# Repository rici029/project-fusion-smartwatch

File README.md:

# InkTime - Smartwatch Open Source

InkTime este un smartwatch ieftin, open-source, construit in jurul microcontroller-ului **Nordic nRF52840** (BLE 5 + ARM Cortex-M4) si a unui display **e-paper de 1.54"**. Consumul redus al e-paper-ului combinat cu eficienta nRF-ului permite o autonomie de cateva zile pe o baterie LiPo mica.

---

## Cuprins

- [Diagrama bloc](#diagrama-bloc)
- [Descriere hardware](#descriere-hardware)
- [Bill of Materials (BOM)](#bill-of-materials-bom)
- [Pin mapping nRF52840](#pin-mapping-nrf52840)
- [Estimare consum energie](#estimare-consum-energie)
- [Design mecanic](#design-mecanic)
- [Design log](#design-log)
- [Structura repository-ului](#structura-repository-ului)
- [Licenta](#licenta)

---

## Diagrama bloc

Arhitectura dispozitivului se bazeaza pe nRF52840 ca hub central. Acesta comunica cu:

- **Display e-paper** prin SPI + semnale de control (DC/RST/BUSY)
- **Accelerometrul BMA423** prin I2C (pentru detectarea miscarii si step counter)
- **PMIC BQ25180** prin I2C (management incarcare baterie Li-Ion)
- **Driver haptic DRV2605** prin I2C (feedback vibrator)
- **USB-C** pentru incarcare si comunicatie seriala (USB nativ al nRF)
- **3 butoane** pe GPIO-uri dedicate
- **Antena chip 2.4GHz** pentru BLE

Alimentarea este furnizata de un buck-boost **RT6160** care genereaza 3.3V stabil din baterie (domeniu tipic 3.0-4.2V).

---

## Descriere hardware

### Microcontroller - Nordic nRF52840

- **Core:** ARM Cortex-M4F @ 64 MHz
- **Memorie:** 1 MB Flash + 256 KB RAM
- **Radio:** BLE 5.3, 2.4 GHz, puterea TX pana la +8 dBm
- **Interfete:** USB 2.0 Full Speed nativ, SPI, I2C, UART, I2S, PDM, QSPI
- **Justificare alegere:** consum redus (~5 uA in System OFF cu RAM retinuta), suport BLE complet, USB nativ care elimina nevoia de USB-to-Serial

### Power Management

**BQ25180 - Battery Charger (IC1)**
- Incarcator Li-Ion de 1 celula, pana la 550 mA
- Protectii integrate: OVP, SCP, termica
- Control prin I2C - poate raporta starea bateriei si curentul de incarcare
- Pin ALERT (interrupt) catre nRF pentru notificare evenimente

**RT6160 - Buck-Boost DC/DC (IC2)**
- Intrare: 2.5-5.5V (acopera atat VBAT cat si VBUS de la USB)
- Iesire: 3.3V (VREG -> 3V3 rail intern)
- Eficienta >90% la sarcini tipice
- Iesirea VSEL configurabila digital

### Senzori

**BMA423 - Accelerometru 3-axe (IC3)**
- 16-bit, range +/-2/+/-4/+/-8/+/-16 g
- Consum ultra-low: ~3 uA in low-power mode
- Features integrate: step counter, wake-on-tilt, activity recognition
- Comunicatie: I2C
- Doua interrupt-uri (INT1, INT2) pentru wake-up asincron al nRF

### Haptic Feedback

**DRV2605 - Haptic Driver (IC4)**
- Driver pentru motor ERM/LRA (shaker coin motor)
- Librarie integrata de 123 efecte preset
- Control I2C + enable digital (HAPTIC_EN)

### Display

**E-paper 1.54" (model WSH-12561, 200x200 pixel)**
- Conectat prin SPI (MOSI, SCK, EPD_CS) + 3 semnale control (DC, RST, BUSY)
- Circuit de boost integrat - foloseste componentele externe EPD_C1..EPD_C12 (condensatoare + inductor L2, L3 + diode D1-D3 pentru generarea PREVGL/PREVGH/GDR)
- Activare alimentare 3.3V prin MOSFET Q2 controlat de EPD_CS

### USB si protectie

**Conector USB-C (J3)** cu 16 pini (reversibil)
**USBLC6-2SC6Y (D4)** - ESD protection pe liniile D+/D-
Conectare directa la nRF52840 (USB nativ integrat)

### Circuit RF

Antena **2450AT18B100E** (Johanson) cu pi-network de matching:
- **C13, C15, C16** - condensatoare de acord
- **L4 (3.9 nH)** - inductor de matching
- **X1 (32 MHz)** - cristal pentru PLL radio, cu condensatoare de sarcina (12pF)
- **X2 (32.768 kHz)** - cristal pentru RTC (wake-up periodic low-power)

---

## Bill of Materials (BOM)

| Ref | Componenta | Valoare / Model | Capsula | Link JLC Parts | Datasheet |
|-----|------------|-----------------|---------|----------------|-----------|
| IC - nRF | Microcontroller | nRF52840-QIAA | aQFN73 | [JLC](https://jlcpcb.com/parts) | [PDF](https://infocenter.nordicsemi.com/pdf/nRF52840_PS_v1.7.pdf) |
| IC1 | Battery Charger PMIC | BQ25180 | WCSP-8 | [JLC](https://jlcpcb.com/parts) | [PDF](https://www.ti.com/lit/ds/symlink/bq25180.pdf) |
| IC2 | Buck-Boost DC/DC | RT6160A | WQFN-15 | [JLC](https://jlcpcb.com/parts) | [PDF](https://www.richtek.com/assets/product_file/RT6160A/DS6160A-00.pdf) |
| IC3 | Accelerometer | BMA423 | LGA-12 | [JLC](https://jlcpcb.com/parts) | [PDF](https://www.bosch-sensortec.com/media/boschsensortec/downloads/datasheets/bst-bma423-ds000.pdf) |
| IC4 | Haptic Driver | DRV2605 | WCSP-9 | [JLC](https://jlcpcb.com/parts) | [PDF](https://www.ti.com/lit/ds/symlink/drv2605.pdf) |
| U1 | Fuel Gauge | (MAX17048 / LC709203) | WCSP-8 | [JLC](https://jlcpcb.com/parts) | [PDF](https://www.analog.com/media/en/technical-documentation/data-sheets/MAX17048-MAX17049.pdf) |
| ANT1 | Chip Antenna 2.4GHz | 2450AT18B100E | SMD | [JLC](https://jlcpcb.com/parts) | [PDF](https://www.johansontechnology.com/datasheets/2450AT18B100/2450AT18B100.pdf) |
| X1 | Cristal | 32 MHz | 3.2x2.5 mm | [JLC](https://jlcpcb.com/parts) | - |
| X2 | Cristal | 32.768 kHz | 3.2x1.5 mm | [JLC](https://jlcpcb.com/parts) | - |
| L1 | Inductor DC/DC | MLP2016 470nH | 2016 | [JLC](https://jlcpcb.com/parts) | - |
| L2 | Inductor E-paper | 10 uH | 0603 | [JLC](https://jlcpcb.com/parts) | - |
| L3 | Inductor E-paper | 15 uH | 0603 | [JLC](https://jlcpcb.com/parts) | - |
| L4 | Inductor RF matching | 3.9 nH | 0201 | [JLC](https://jlcpcb.com/parts) | - |
| Q2 | MOSFET P-channel | (EPD power switch) | SOT-23 | [JLC](https://jlcpcb.com/parts) | - |
| D1-D3 | Dioda Schottky | (boost converter) | SOD-323 | [JLC](https://jlcpcb.com/parts) | - |
| D4 | ESD USB Protection | USBLC6-2SC6Y | SOT-23-6 | [JLC](https://jlcpcb.com/parts) | [PDF](https://www.st.com/resource/en/datasheet/usblc6-2.pdf) |
| J1 | SWD Programming | TC2030-IDC | THT | [JLC](https://jlcpcb.com/parts) | [PDF](https://www.tag-connect.com/wp-content/uploads/bsk-pdf-manager/TC2030-IDC_Datasheet_14.pdf) |
| J2 | FPC Connector | 503480-2400 (24p) | SMD | [JLC](https://jlcpcb.com/parts) | [PDF](https://www.molex.com/pdm_docs/sd/5034802400_sd.pdf) |
| J3 | USB-C | KH-TYPE-C-16P | SMD | [JLC](https://jlcpcb.com/parts) | - |
| SW1-3 | Buton tactil | SMD side-push | SMD | [JLC](https://jlcpcb.com/parts) | - |
| Baterie | LiPo 3.7V | AKY0106 | - | - | [PDF](https://www.tme.eu/Document/b9e12bf26ad0ba929a22ab5d58f022cd/AKY0106.pdf) |
| Display | E-paper 1.54" | WSH-12561 | FPC | - | [PDF](https://www.tme.eu/Document/0ca57a8ffbcd57b5bca53252eb9d6ec3/WSH-12561.pdf) |
| Shaker | Motor vibrator | DFRobot FIT0774 | coin | - | [link](https://www.tme.eu/ro/details/df-fit0774/motoare-dc/dfrobot/fit0774/) |

**Condensatoare si rezistente:** toate in capsule 0201 (pentru valori <= 100 nF) sau 0402 (pentru valori > 100 nF), conform cerintei proiectului. Vezi fisierul `Manufacturing/bom.txt` pentru lista completa cu referinte si valori.

---

## Pin mapping nRF52840

| Pin nRF52840 | Net / Semnal | Functie | Motivatie alegere |
|--------------|--------------|---------|-------------------|
| P0.26 | SCL | I2C Clock | Pin GPIO standard, aproape de IC-urile I2C (BMA423, BQ25180, DRV2605) pentru trase scurte |
| P0.27 | SDA | I2C Data | Pereche cu P0.26 pentru TWI0 |
| P0.04 | IMU_INT1 | Interrupt BMA423 | Pin cu capabilitate AIN (ADC) dar folosit ca GPIO - pozitie convenabila pe PCB |
| P0.13 | SCK | SPI Clock (E-paper) | High-speed GPIO, suport SPIM |
| P0.14 | MOSI | SPI Data (E-paper) | Pereche cu SCK pe aceeasi periferica SPIM |
| P0.19 | EPD_CS | Chip Select e-paper | GPIO simplu, control SPI CS |
| P0.20 | EPD_DC | Data/Command | Control semnal pentru display |
| P0.21 | EPD_RST | Reset e-paper | GPIO cu output drive standard |
| P0.22 | EPD_BUSY | Busy signal | Input de la display, pentru polling |
| P0.23 | HAPTIC_EN | Enable DRV2605 | GPIO simplu, activeaza driver-ul haptic |
| P0.24 | PMIC_INT | Interrupt BQ25180 | Interrupt la evenimente de charging |
| P0.25 | ALERT | Alert fuel gauge | Notificare low-battery |
| P0.09, P0.10 | SW1, SW2 (Buttons) | Butoane utilizator | Pini dedicati cu suport NFC dezactivat (configurabili GPIO) |
| P1.09 | SW3 | Al treilea buton | GPIO free pe portul P1 |
| P1.01 | IMU_INT2 | Interrupt secundar BMA423 | GPIO free |
| SWDIO, SWDCLK | TP + J1 | Programming / Debug | Pini dedicati SWD, accesibili prin TC2030 si test pad-uri |
| XL1, XL2 | X2 (32.768 kHz) | LFCLK pentru RTC | Pini dedicati oscilatorului low-frequency |
| XC1, XC2 | X1 (32 MHz) | HFCLK pentru radio | Pini dedicati oscilatorului high-frequency |
| D+/D- | USB | USB native | Pini dedicati, conectati direct la USB-C prin USBLC6 |
| ANT | ANT1 | Antena BLE | Pin RF dedicat, conectat prin reteaua de matching |

**Nota:** Pinii ADC (P0.02-P0.05, P0.28-P0.31) care nu sunt folositi ca AIN sunt disponibili pentru extensii viitoare (ex: senzori analogici aditionali).

---

## Estimare consum energie

| Mod de operare | Componente active | Consum estimat |
|----------------|-------------------|----------------|
| Sleep (System OFF + RAM) | nRF RAM retained + RTC + BMA423 low-power | **~10 uA** |
| Idle (display static, BLE advertising) | nRF BLE adv + RTC + IMU | **~50 uA** |
| Active (refresh display) | nRF MCU on + SPI + EPD boost | ~8 mA (~500 ms per refresh) |
| BLE connected (data transfer) | nRF radio TX/RX @ 0 dBm | ~5-8 mA |
| Charging | BQ25180 la 500 mA | de la USB, nu de la baterie |

**Autonomie estimata:**  
Baterie tipica: ~110 mAh (AKY0106).  
Cu consum mediu ~50 uA (majoritatea timpului in idle + cateva refresh-uri de display pe ora):

T_autonomie = 110 mAh / 0.05 mA = 2200 ore ~ 90 zile

In practica, cu uzura normala (notificari, interactiuni cu butoanele, sync BLE), **durata de viata realista pe baterie este de ~2-4 saptamani**.

---

## Design mecanic

Dispozitivul este construit din:
- **PCB 1 mm grosime**, 4 layere (Top + 2 Inner GND + Bottom)
- **Carcasa** cu TopCase (rama + fereastra display) + BottomCase (compartiment baterie)
- **Baterie LiPo** plasata sub PCB in compartimentul BottomCase
- **Display e-paper** montat deasupra PCB, aliniat cu fereastra TopCase
- **Shaker motor** plasat lateral, conectat la PCB prin pad-uri TP_OUT+/OUT-
- **3 butoane fizice** aliniate cu SW1-SW3 pe PCB

Bateria se conecteaza direct la 2 test pad-uri (TP_BAT / TP_GND) in loc sa foloseasca conectorul JST original, pentru a economisi spatiu.

---

## Design log

### Decizii importante luate

1. **Alegerea stack-up-ului 4 layere:** desi un design 2-layer ar fi fost posibil, am optat pentru 4 layere cu doua planuri GND interne (Optiunea B). Motivele:
   - Return path continuu pentru semnalele SPI (display) si USB D+/D-
   - Performanta RF mai buna pentru circuitul BLE 2.4 GHz
   - Simplificare rutare - nu mai trebuie evitate via-urile pe trasee de putere
   - Ecranare EMI imbunatatita intre TOP si BOTTOM

2. **Rutarea 3V3 ca trasee groase (nu plane):** pentru ca 3V3 e consumator redus (< 100 mA) am preferat trasee groase (0.3 mm) pe TOP/BOTTOM in loc de un plane intern. Inner layers raman ambele GND.

3. **Antena la marginea PCB-ului + decupare:** am plasat antena 2450AT18B100E la marginea placii, cu zona de sub ea **decupata mecanic** si fara cupru pe niciun layer (conform datasheet si cerintei). In jurul antenei am adaugat via stitching pentru a lega planurile GND.

4. **Keepout pe toate cele 4 layere sub antena:** am desenat dreptunghiuri pe tRestrict, bRestrict si echivalentele pentru inner layers, plus decupare pe Dimension/Milling.

5. **Via stitching in zona RF:** plasate via-uri GND (0.3 mm drill / 0.6 mm diametru) la ~1.5 mm distanta in jurul nRF52840 si antenei pentru continuitate planuri GND.

6. **Plasarea condensatoarelor de decuplare:** toate cele 100 nF sunt plasate in capsula 0201 direct langa pinii VDD ai nRF, BMA423, DRV2605, BQ25180 si RT6160.

### Probleme intampinate

- **Rutare sub BGA nRF52840:** pinii interni ai BGA-ului au spatiere foarte mica; traseele de intrare/iesire din zona BGA au fost ingustate la 0.127 mm pentru a se incadra intre bile. Au aparut erori DRC "width too small" dar sunt acceptate conform cerintei.
- **Spatiu limitat pentru rutare:** placa de smartwatch fiind compacta (~35x40 mm), am trecut la 4 layere pentru a avea suficient spatiu de rutare.
- **Orientarea FPC-ului display-ului:** conectorul J2 a fost orientat astfel incat cablul flat sa aiba lungime minima pana la display, fara bucle.
- **Net classes aplicate dupa ce am inceput rutarea:** am adaugat clasa "Power" cu width 0.3 mm dupa ce rutasem deja cateva trasee la 0.15 mm. Am folosit comanda CHANGE WIDTH pentru a le ingrosa.

---

## Structura repository-ului

```
InkTime/
├── Hardware/
│   ├── InkTime_Schematic.sch     # Schematicul Fusion
│   ├── InkTime_Schematic.brd     # Board-ul Fusion
│   └── InkTime_Schematic.pdf     # Print-out schematic
├── Manufacturing/
│   ├── gerbers.zip               # Fisiere Gerber + Drill
│   ├── bom.txt                   # Bill of Materials
│   └── cpl.txt                   # Pick and Place
├── Mechanical/
│   ├── complete_device.step      # Model 3D exploded
│   └── complete_device.f3z       # Fisier Fusion Design complet
├── Images/
│   ├── block_diagram.png
│   ├── pcb_top.png
│   ├── pcb_bottom.png
│   ├── pcb_3d_top.png
│   └── device_3d.png
├── LICENSE                       # Apache 2.0
└── README.md
```

---

## Licenta

Acest proiect este licentiat sub **Apache License 2.0**. Vezi fisierul [LICENSE](LICENSE) pentru detalii.

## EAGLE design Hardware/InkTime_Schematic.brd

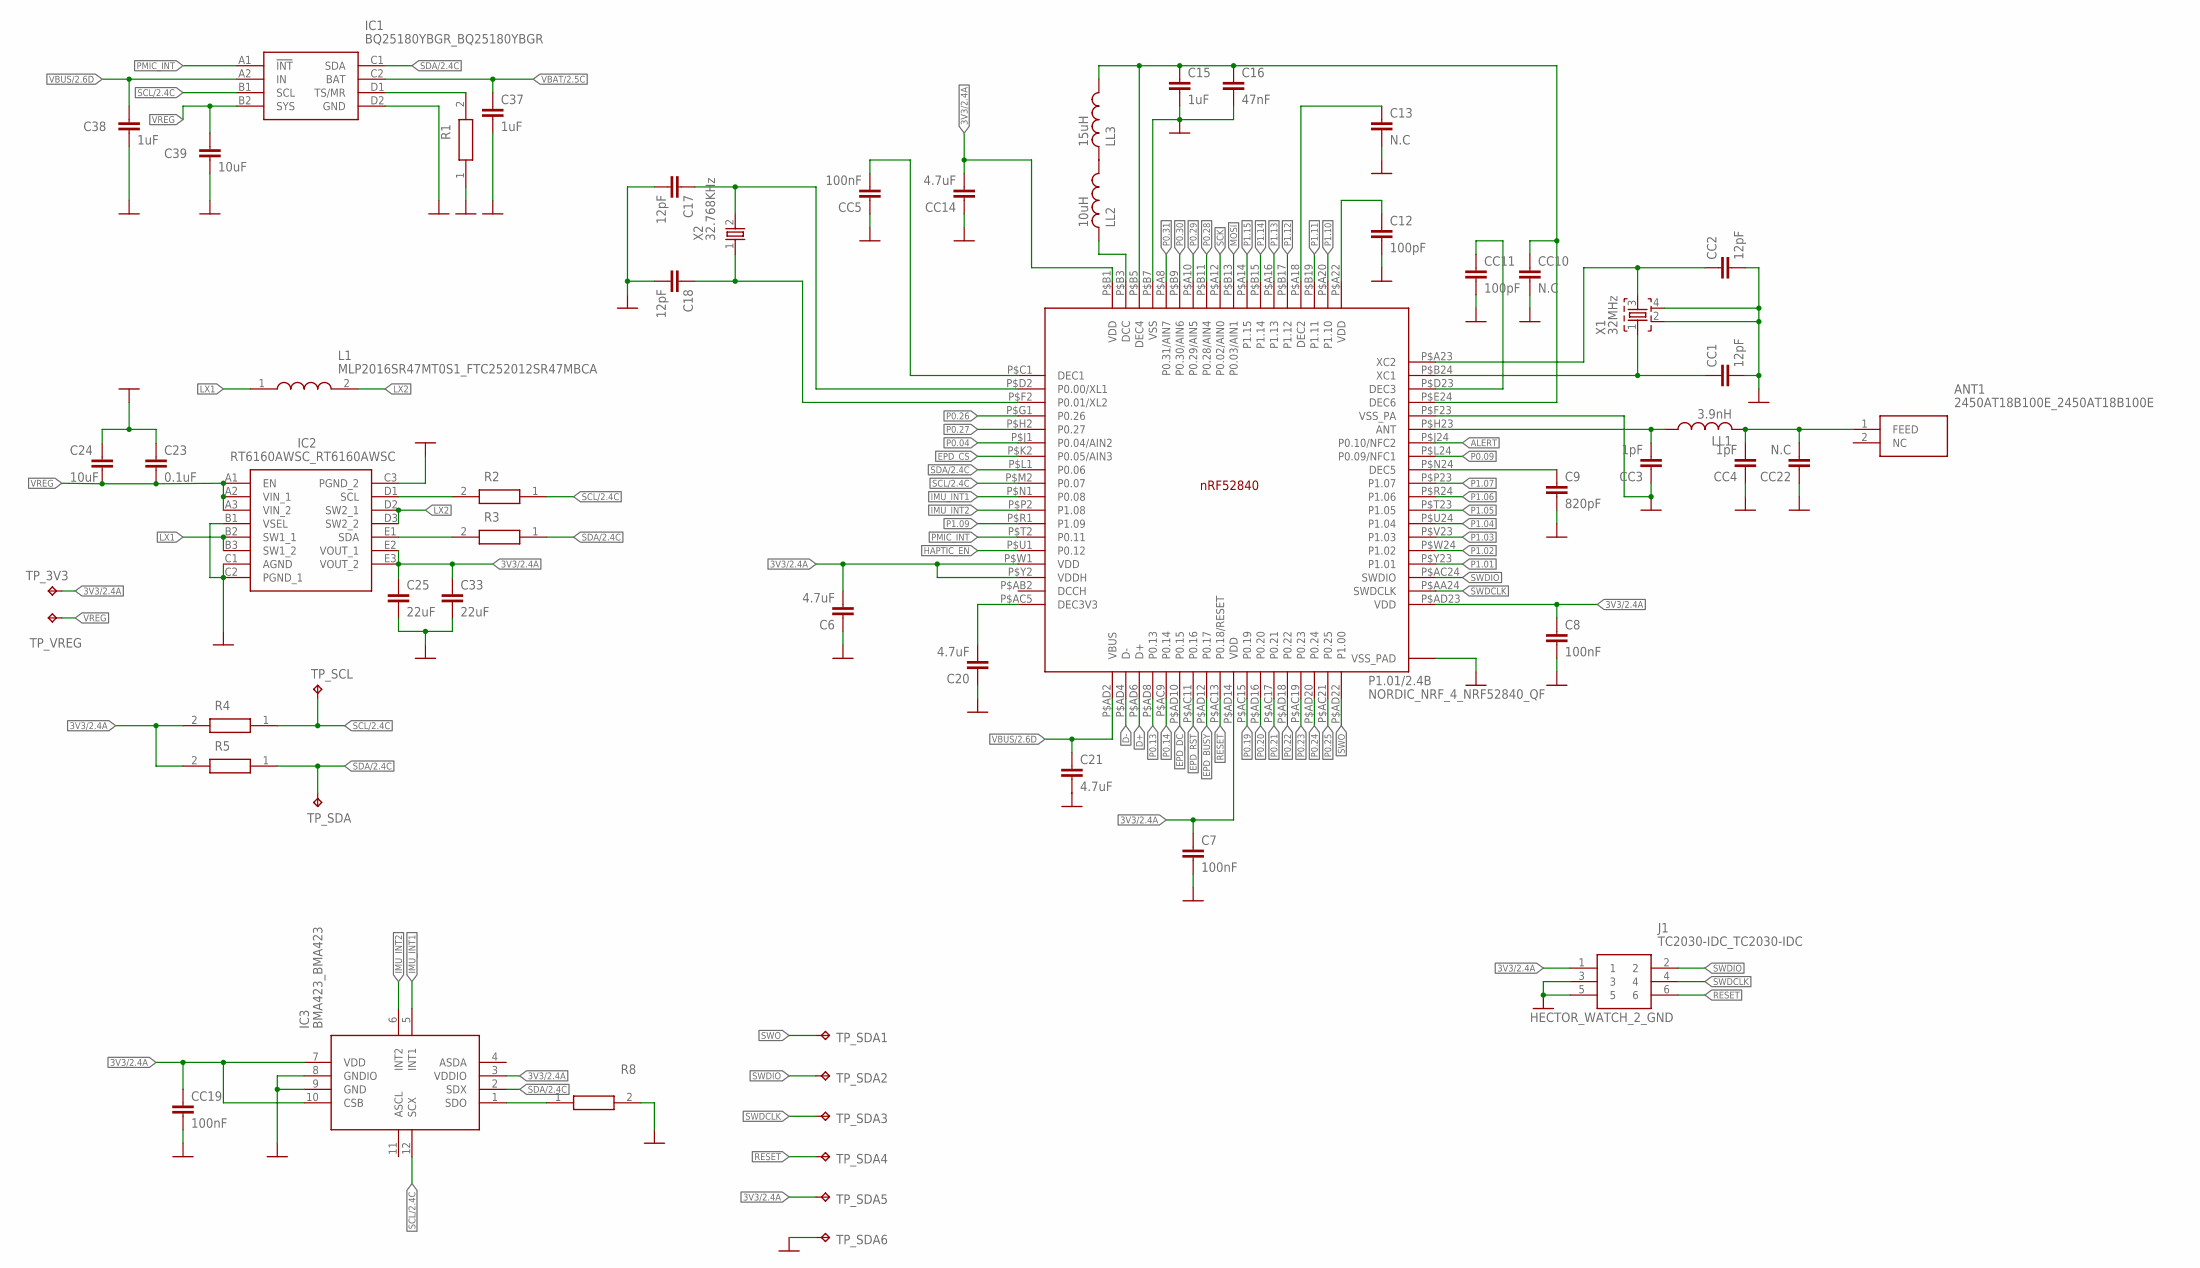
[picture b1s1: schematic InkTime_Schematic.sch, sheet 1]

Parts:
ANT1: 2450AT18B100E_2450AT18B100E; 2450AT18B100E_ANTC3216X140N
C6, C20, C21: 4.7uF; NORDIC_NRF_3_RESC0402_M
C7, C8: 100nF; NORDIC_NRF_3_RESC0402_M
C9: 820pF; NORDIC_NRF_3_RESC0402_M
C12: 100pF; NORDIC_NRF_3_RESC0402_M
C13: N.C; NORDIC_NRF_3_RESC0402_M
C15, C37, C38: 1uF; NORDIC_NRF_3_RESC0402_M
C16: 47nF; NORDIC_NRF_3_RESC0402_M
C17, C18: 12pF; NORDIC_NRF_3_RESC0402_M
C23: 0.1uF; NORDIC_NRF_3_RESC0402_M
C24, C39: 10uF; NORDIC_NRF_3_RESC0402_M
C25, C33: 22uF; NORDIC_NRF_3_RESC0402_M
CC1, CC2: 12pF; NORDIC_NRF_3_RESC0402_M
CC3, CC4: 1pF; NORDIC_NRF_3_RESC0402_M
CC5, CC19: 100nF; NORDIC_NRF_3_RESC0402_M
CC10, CC22: N.C; NORDIC_NRF_3_RESC0402_M
CC11: 100pF; NORDIC_NRF_3_RESC0402_M
CC14: 4.7uF; NORDIC_NRF_3_RESC0402_M
IC1: BQ25180YBGR_BQ25180YBGR; BQ25180YBGR_BGA8C40P2X4_100X155X50
IC2: RT6160AWSC_RT6160AWSC; RT6160AWSC_BGA15C40P3X5_140X230X60
IC3: BMA423_BMA423
J1: TC2030-IDC_TC2030-IDC; TC2030-IDC_TC2030IDC
L1: MLP2016SR47MT0S1_FTC252012SR47MBCA; MLP2016SR47MT0S1_INDC2016X100N
LL1: 3.9nH; NORDIC_NRF_2_RESC0402_M
LL2: 10uH; NORDIC_NRF_2_RESC0402_M
LL3: 15uH; NORDIC_NRF_2_RESC0402_M
P1.01/2.4B: NORDIC_NRF_4_NRF52840_QF; NORDIC_NRF_4_AQFN50P700X700X85_HS-74N
R1: 10K; CPF0201D7K68C1_0201
R2, R3, R4, R5, R8: CPF0201D7K68C1_CPF0201D7K68C1; CPF0201D7K68C1_0201
TP_3V3: HECTOR_WATCH_1_TPTP20R; HECTOR_WATCH_1_TP20R
TP_SCL: HECTOR_WATCH_1_TPTP20R; HECTOR_WATCH_1_TP20R
TP_SDA, TP_SDA1, TP_SDA2, TP_SDA3, TP_SDA4, TP_SDA5, TP_SDA6: HECTOR_WATCH_1_TPTP20R; HECTOR_WATCH_1_TP20R
TP_VREG: HECTOR_WATCH_1_TPTP20R; HECTOR_WATCH_1_TP20R
X1: 32MHz; NORDIC_NRF_BT-XTAL_2016_N
X2: 32.768KHz; NORDIC_NRF_1_XTAL_3215_N

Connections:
3V3/2.4A: C6.2, C7.1, C8.1, C25.1, C33.1, CC14.2, CC19.1, IC2.E2 (VOUT_1), IC2.E3 (VOUT_2), IC3.3 (VDDIO), IC3.7 (VDD), IC3.10 (CSB), J1.1, P1.01/2.4B.P$AD14 (VDD), P1.01/2.4B.P$AD23 (VDD), P1.01/2.4B.P$B1 (VDD), P1.01/2.4B.P$W1 (VDD), P1.01/2.4B.P$Y2 (VDDH), R4.2, R5.2, TP_3V3.TP, TP_SDA5.TP
ALERT: P1.01/2.4B.P$J24 (P0.10/NFC2); also elsewhere on the board
D+: P1.01/2.4B.P$AD6 (D+); also elsewhere on the board
D-: P1.01/2.4B.P$AD4 (D-); also elsewhere on the board
EPD_BUSY: P1.01/2.4B.P$AD12 (P0.17); also elsewhere on the board
EPD_CS: P1.01/2.4B.P$K2 (P0.05/AIN3); also elsewhere on the board
EPD_DC: P1.01/2.4B.P$AD10 (P0.15); also elsewhere on the board
EPD_RST: P1.01/2.4B.P$AC11 (P0.16); also elsewhere on the board
GND: C6.1, C7.2, C8.2, C9.2, C12.2, C13.2, C15.2, C16.2, C17.2, C18.2, C20.1, C21.2, C23.1, C24.1, C25.2, C33.2, C37.2, C38.2, C39.2, CC1.2, CC2.2, CC3.1, CC4.1, CC5.1, CC10.2, CC11.2, CC14.1, CC19.2, CC22.1, IC1.D2 (GND), IC2.B1 (VSEL), IC2.C1 (AGND), IC2.C2 (PGND_1), IC2.C3 (PGND_2), IC3.8 (GNDIO), IC3.9 (GND), J1.3, J1.5, P1.01/2.4B.P$74 (VSS_PAD), P1.01/2.4B.P$75 (VSS_PAD), P1.01/2.4B.P$76 (VSS_PAD), P1.01/2.4B.P$77 (VSS_PAD), P1.01/2.4B.P$78 (VSS_PAD), P1.01/2.4B.P$79 (VSS_PAD), P1.01/2.4B.P$80 (VSS_PAD), P1.01/2.4B.P$81 (VSS_PAD), P1.01/2.4B.P$82 (VSS_PAD), P1.01/2.4B.P$83 (VSS_PAD), P1.01/2.4B.P$84 (VSS_PAD), P1.01/2.4B.P$85 (VSS_PAD), P1.01/2.4B.P$86 (VSS_PAD), P1.01/2.4B.P$87 (VSS_PAD), P1.01/2.4B.P$88 (VSS_PAD), P1.01/2.4B.P$89 (VSS_PAD), P1.01/2.4B.P$90 (VSS_PAD), P1.01/2.4B.P$B7 (VSS), P1.01/2.4B.P$F23 (VSS_PA), R1.1, R8.2, TP_SDA6.TP, X1.2, X1.4; also elsewhere on the board
HAPTIC_EN: P1.01/2.4B.P$U1 (P0.12); also elsewhere on the board
IMU_INT1: IC3.5 (INT1), P1.01/2.4B.P$N1 (P0.08)
IMU_INT2: IC3.6 (INT2), P1.01/2.4B.P$P2 (P1.08)
LX1: IC2.B2 (SW1_1), IC2.B3 (SW1_2), L1.1
LX2: IC2.D2 (SW2_1), IC2.D3 (SW2_2), L1.2
MOSI: P1.01/2.4B.P$B13 (P0.03/AIN1); also elsewhere on the board
unnamed: IC1.D1 (TS/MR), R1.2
unnamed: C9.1, P1.01/2.4B.P$N24 (DEC5)
unnamed: CC3.2, LL1.1, P1.01/2.4B.P$H23 (ANT)
unnamed: IC2.D1 (SCL), R2.2
unnamed: IC2.E1 (SDA), R3.2
unnamed: C20.2, P1.01/2.4B.P$AC5 (DEC3V3)
unnamed: ANT1.1 (FEED), CC4.2, CC22.2, LL1.2
unnamed: CC1.1, P1.01/2.4B.P$B24 (XC1), X1.1
unnamed: CC2.1, P1.01/2.4B.P$A23 (XC2), X1.3
unnamed: CC11.1, P1.01/2.4B.P$D23 (DEC3)
unnamed: C18.1, P1.01/2.4B.P$F2 (P0.01/XL2), X2.1
unnamed: C12.1, P1.01/2.4B.P$A22 (VDD)
unnamed: C13.1, P1.01/2.4B.P$A18 (DEC2)
unnamed: LL2.1, LL3.2
unnamed: LL2.2, P1.01/2.4B.P$B3 (DCC)
unnamed: C15.1, C16.1, CC10.1, LL3.1, P1.01/2.4B.P$B5 (DEC4), P1.01/2.4B.P$E24 (DEC6)
unnamed: C17.1, P1.01/2.4B.P$D2 (P0.00/XL1), X2.2
unnamed: IC3.1 (SDO), R8.1
unnamed: CC5.2, P1.01/2.4B.P$C1 (DEC1)
P0.04: P1.01/2.4B.P$J1 (P0.04/AIN2)
P0.09: P1.01/2.4B.P$L24 (P0.09/NFC1)
P0.13: P1.01/2.4B.P$AD8 (P0.13); also elsewhere on the board
P0.14: P1.01/2.4B.P$AC9 (P0.14); also elsewhere on the board
P0.19: P1.01/2.4B.P$AC15 (P0.19)
P0.20: P1.01/2.4B.P$AD16 (P0.20)
P0.21: P1.01/2.4B.P$AC17 (P0.21)
P0.22: P1.01/2.4B.P$AD18 (P0.22)
P0.23: P1.01/2.4B.P$AC19 (P0.23)
P0.24: P1.01/2.4B.P$AD20 (P0.24)
P0.25: P1.01/2.4B.P$AC21 (P0.25)
P0.26: P1.01/2.4B.P$G1 (P0.26)
P0.27: P1.01/2.4B.P$H2 (P0.27)
P0.28: P1.01/2.4B.P$B11 (P0.28/AIN4)
P0.29: P1.01/2.4B.P$A10 (P0.29/AIN5)
P0.30: P1.01/2.4B.P$B9 (P0.30/AIN6)
P0.31: P1.01/2.4B.P$A8 (P0.31/AIN7)
P1.01: P1.01/2.4B.P$Y23 (P1.01); also elsewhere on the board
P1.02: P1.01/2.4B.P$W24 (P1.02); also elsewhere on the board
P1.03: P1.01/2.4B.P$V23 (P1.03)
P1.04: P1.01/2.4B.P$U24 (P1.04)
P1.05: P1.01/2.4B.P$T23 (P1.05)
P1.06: P1.01/2.4B.P$R24 (P1.06)
P1.07: P1.01/2.4B.P$P23 (P1.07)
P1.09: P1.01/2.4B.P$R1 (P1.09)
P1.10: P1.01/2.4B.P$A20 (P1.10)
P1.11: P1.01/2.4B.P$B19 (P1.11)
P1.12: P1.01/2.4B.P$B17 (P1.12)
P1.13: P1.01/2.4B.P$A16 (P1.13)
P1.14: P1.01/2.4B.P$B15 (P1.14)
P1.15: P1.01/2.4B.P$A14 (P1.15)
PMIC_INT: IC1.A1 (!INT), P1.01/2.4B.P$T2 (P0.11)
RESET: J1.6, P1.01/2.4B.P$AC13 (P0.18/RESET), TP_SDA4.TP
SCK: P1.01/2.4B.P$A12 (P0.02/AIN0); also elsewhere on the board
SCL/2.4C: IC1.B1 (SCL), IC3.12 (SCX), P1.01/2.4B.P$M2 (P0.07), R2.1, R4.1, TP_SCL.TP
SDA/2.4C: IC1.C1 (SDA), IC3.2 (SDX), P1.01/2.4B.P$L1 (P0.06), R3.1, R5.1, TP_SDA.TP
SWDCLK: J1.4, P1.01/2.4B.P$AA24 (SWDCLK), TP_SDA3.TP
SWDIO: J1.2, P1.01/2.4B.P$AC24 (SWDIO), TP_SDA2.TP
SWO: P1.01/2.4B.P$AD22 (P1.00), TP_SDA1.TP
VBAT/2.5C: C37.1, IC1.C2 (BAT)
VBUS/2.6D: C21.1, C38.1, IC1.A2 (IN), P1.01/2.4B.P$AD2 (VBUS)
VREG: C23.2, C24.2, C39.1, IC1.B2 (SYS), IC2.A1 (EN), IC2.A2 (VIN_1), IC2.A3 (VIN_2), TP_VREG.TP

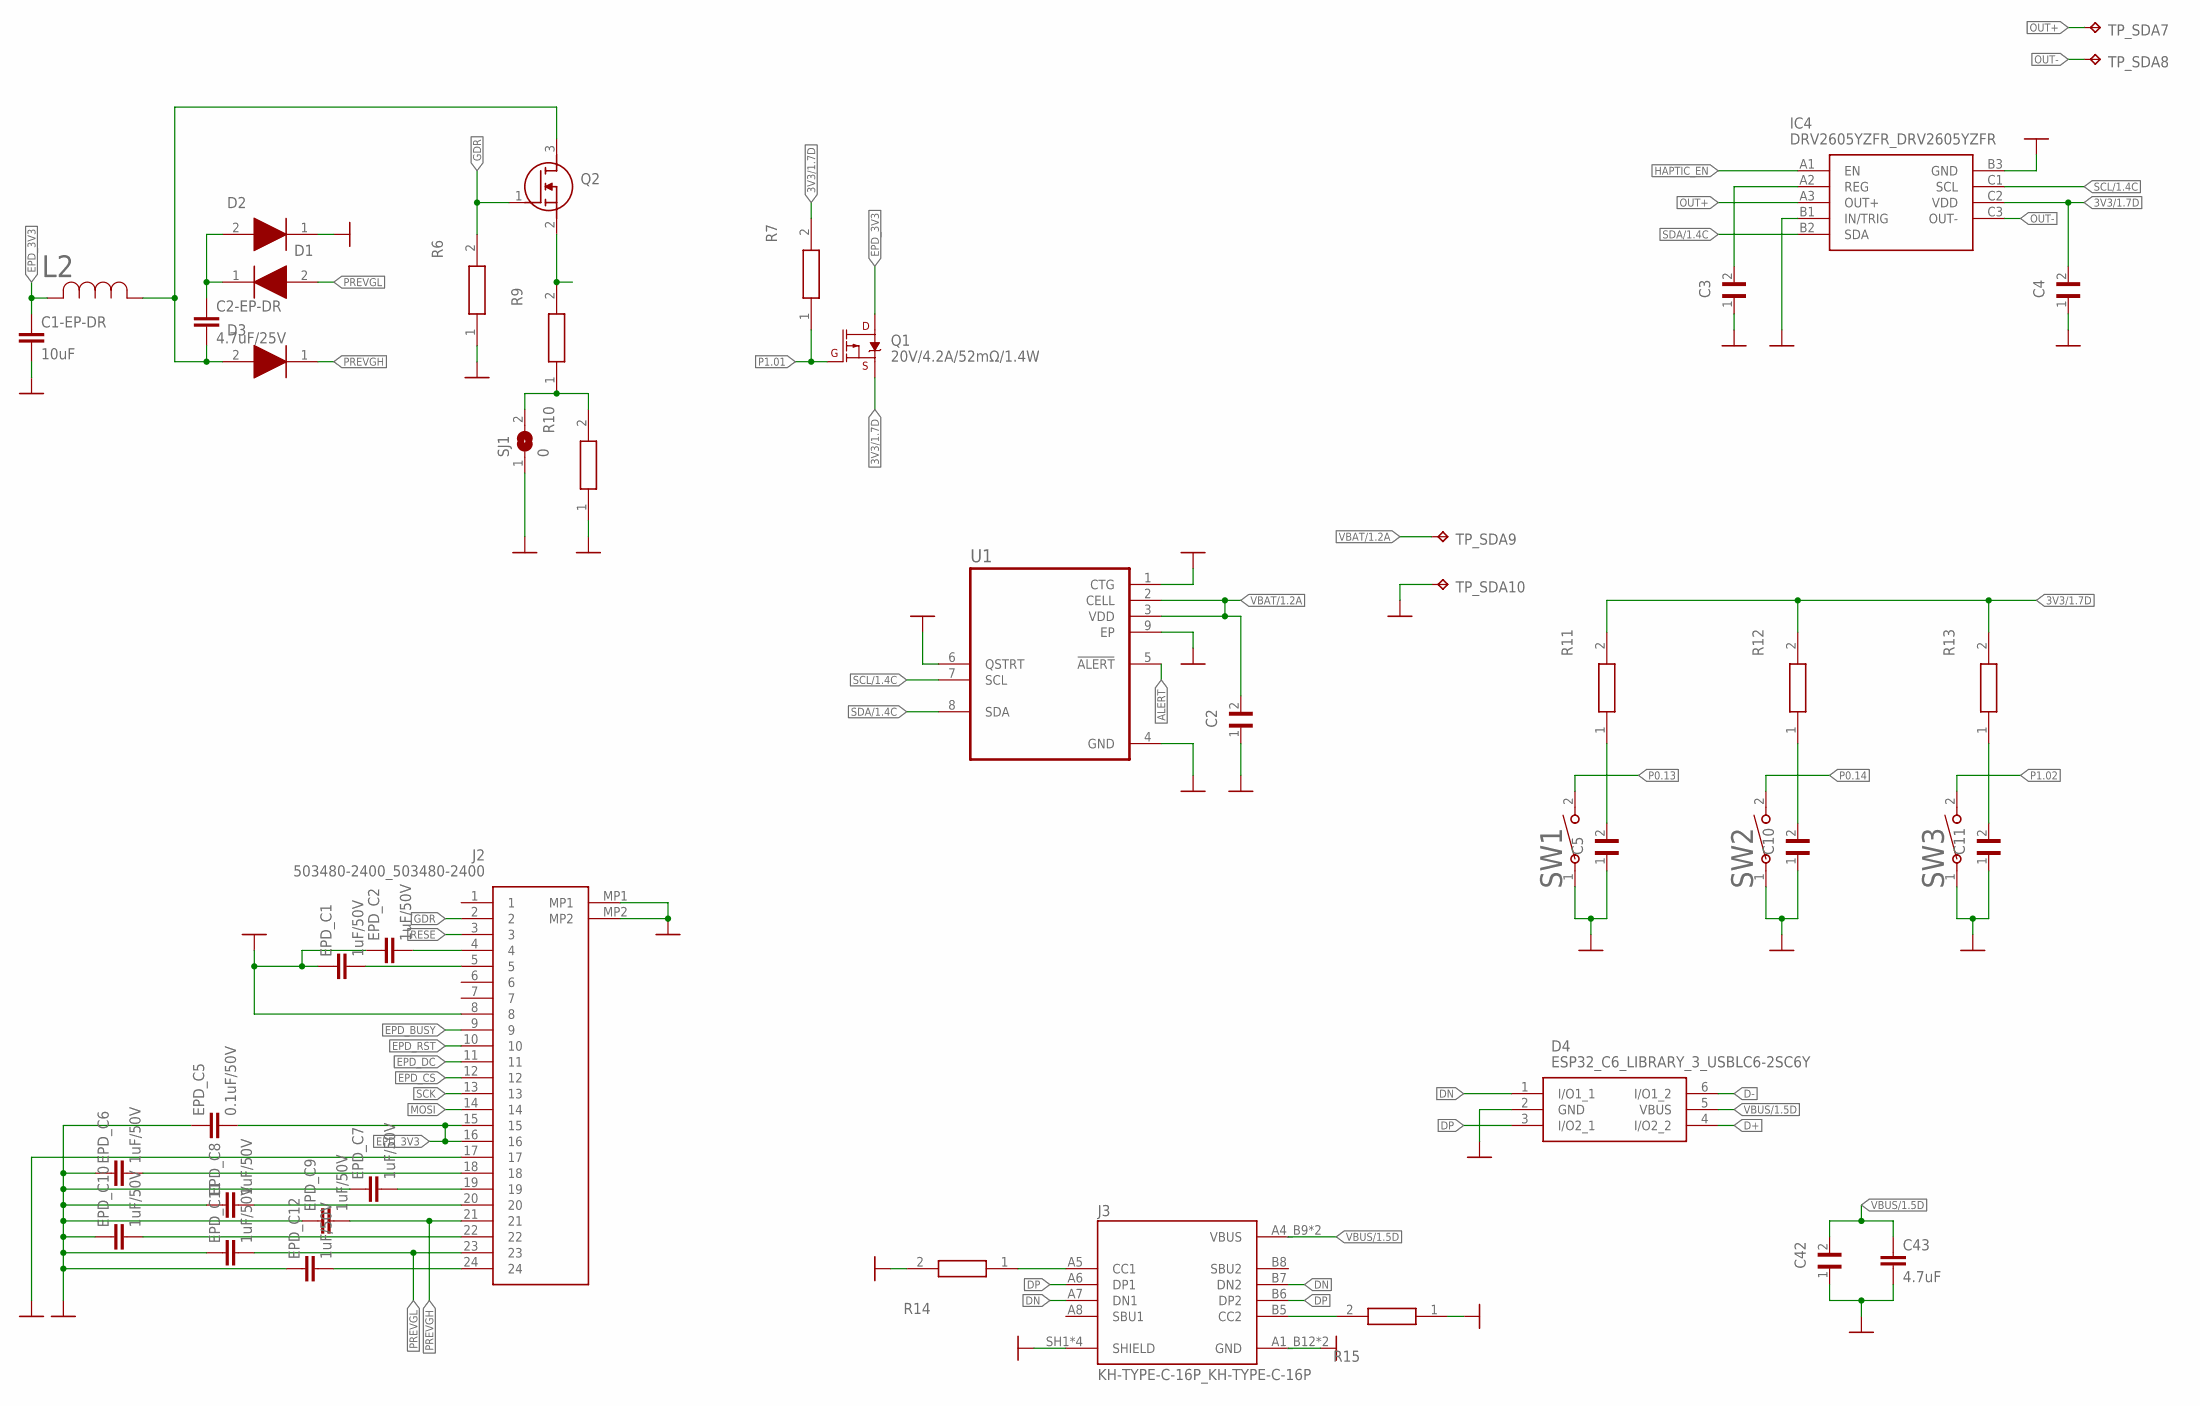
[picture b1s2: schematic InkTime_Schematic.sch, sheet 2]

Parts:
C1-EP-DR: 10uF; NORDIC_NRF_3_RESC0402_M
C2, C5, C10, C11, C42: GRM011R60J152KE01L_1_GRM011R60J152KE01L; GRM011R60J152KE01L_1_0201
C2-EP-DR: 4.7uF/25V; ESP32_C6_LIBRARY_1_ESP32_WROVER_EAGLE-LTSPICE_C0402
C3: 1uF; GRM011R60J152KE01L_1_0201
C4: 0.1uF; GRM011R60J152KE01L_1_0201
C43: 4.7uF; NORDIC_NRF_3_RESC0402_M
D1, D2, D3: ESP32_C6_LIBRARY_5_MBR0530; ESP32_C6_LIBRARY_5_SOD3716X135N
D4: ESP32_C6_LIBRARY_3_USBLC6-2SC6Y; ESP32_C6_LIBRARY_3_SOT95P280X145-6N
EPD_C1, EPD_C2, EPD_C6, EPD_C7, EPD_C8, EPD_C9, EPD_C10, EPD_C11, EPD_C12: 1uF/50V; NORDIC_NRF_3_RESC0402_M
EPD_C5: 0.1uF/50V; NORDIC_NRF_3_RESC0402_M
IC4: DRV2605YZFR_DRV2605YZFR; DRV2605YZFR_BGA9C50P3X3_144X144X62
J2: 503480-2400_503480-2400; 503480-2400_5034802400
J3: KH-TYPE-C-16P_KH-TYPE-C-16P; KH-TYPE-C-16P_KINGHELM_KH-TYPE-C-16P
L2: ESP32_C6_LIBRARY_2_744043680IND_4828-WE-TPC_WRE; ESP32_C6_LIBRARY_2_IND_4828-WE-TPC_WRE
Q1: 20V/4.2A/52mΩ/1.4W; ESP32_C6_LIBRARY_4_ESP32_C6_LIBRARY_4_ESP32_C6_LIBRARY_4_ES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
Q2: ESP32_C6_LIBRARY_6_SI1308EDL-T1-GE3; ESP32_C6_LIBRARY_6_SOT65P210X110-3N
R6, R7, R9, R10, R11, R12, R13, R14, R15: CPF0201D7K68C1_CPF0201D7K68C1; CPF0201D7K68C1_0201
SJ1: 0; ESP32_C6_LIBRARY_7_JUMPER_SJ
SW1, SW2, SW3: 2025-10-22_07-23-44_LIBRARY_EVP-AKE31ASW_EVP-AKE3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; 2025-10-22_07-23-44_LIBRARY_SW_EVP-AKE31A_PAN
TP_SDA7, TP_SDA8, TP_SDA9, TP_SDA10: HECTOR_WATCH_1_TPTP20R; HECTOR_WATCH_1_TP20R
U1: ESP32_C6_LIBRARY_MAX17048G+T10; ESP32_C6_LIBRARY_SON50P200X200X80-9N

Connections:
3V3/1.7D: C4.2, IC4.C2 (VDD), Q1.2 (S), R7.2, R11.2, R12.2, R13.2
ALERT: U1.5 (!ALERT); also elsewhere on the board
D+: D4.4 (I/O2_2); also elsewhere on the board
D-: D4.6 (I/O1_2); also elsewhere on the board
DN: D4.1 (I/O1_1), J3.A7 (DN1), J3.B7 (DN2)
DP: D4.3 (I/O2_1), J3.A6 (DP1), J3.B6 (DP2)
EPD_3V3: C1-EP-DR.1, EPD_C5.2, J2.15, J2.16, L2.2, Q1.3 (D)
EPD_BUSY: J2.9; also elsewhere on the board
EPD_CS: J2.12; also elsewhere on the board
EPD_DC: J2.11; also elsewhere on the board
EPD_RST: J2.10; also elsewhere on the board
GDR: J2.2, Q2.1 (G), R6.2
GND: C1-EP-DR.2, C2.1, C3.1, C4.1, C5.1, C10.1, C11.1, C42.1, C43.2, D2.1 (K), D4.2 (GND), EPD_C1.1, EPD_C2.1, EPD_C5.1, EPD_C6.1, EPD_C7.1, EPD_C8.1, EPD_C9.1, EPD_C10.1, EPD_C11.1, EPD_C12.1, IC4.B1 (IN/TRIG), IC4.B3 (GND), J2.8, J2.17, J2.MP1, J2.MP2, J3.A1_B12 (GND), J3.A12_B1 (GND), J3.SH1 (SHIELD), J3.SH2 (SHIELD), J3.SH3 (SHIELD), J3.SH4 (SHIELD), R6.1, R10.1, R14.2, R15.1, SJ1.1, SW1.1, SW2.1, SW3.1, TP_SDA10.TP, U1.1 (CTG), U1.4 (GND), U1.6 (QSTRT), U1.9 (EP); also elsewhere on the board
HAPTIC_EN: IC4.A1 (EN); also elsewhere on the board
MOSI: J2.14; also elsewhere on the board
unnamed: C2-EP-DR.1, D1.1 (K), D2.2 (A)
unnamed: Q2.2 (S), R9.2
unnamed: R9.1, R10.2, SJ1.2
unnamed: C2-EP-DR.2, D3.2 (A), L2.1, Q2.3 (D)
unnamed: EPD_C2.2, J2.4
unnamed: EPD_C1.2, J2.5
unnamed: J3.B5 (CC2), R15.2
unnamed: EPD_C7.2, J2.19
unnamed: C5.2, R11.1
unnamed: EPD_C12.2, J2.24
unnamed: EPD_C6.2, J2.18
unnamed: EPD_C8.2, J2.20
unnamed: C10.2, R12.1
unnamed: EPD_C10.2, J2.22
unnamed: C11.2, R13.1
unnamed: J3.A5 (CC1), R14.1
unnamed: C3.2, IC4.A2 (REG)
OUT+: IC4.A3 (OUT+), TP_SDA7.TP
OUT-: IC4.C3 (OUT-), TP_SDA8.TP
P0.13: SW1.2; also elsewhere on the board
P0.14: SW2.2; also elsewhere on the board
P1.01: Q1.1 (G), R7.1; also elsewhere on the board
P1.02: SW3.2; also elsewhere on the board
PREVGH: D3.1 (K), EPD_C9.2, J2.21
PREVGL: D1.2 (A), EPD_C11.2, J2.23
RESE: J2.3
SCK: J2.13; also elsewhere on the board
SCL/1.4C: IC4.C1 (SCL), U1.7 (SCL)
SDA/1.4C: IC4.B2 (SDA), U1.8 (SDA)
VBAT/1.2A: C2.2, TP_SDA9.TP, U1.2 (CELL), U1.3 (VDD)
VBUS/1.5D: C42.2, C43.1, D4.5 (VBUS), J3.A4_B9 (VBUS), J3.A9_B4 (VBUS)

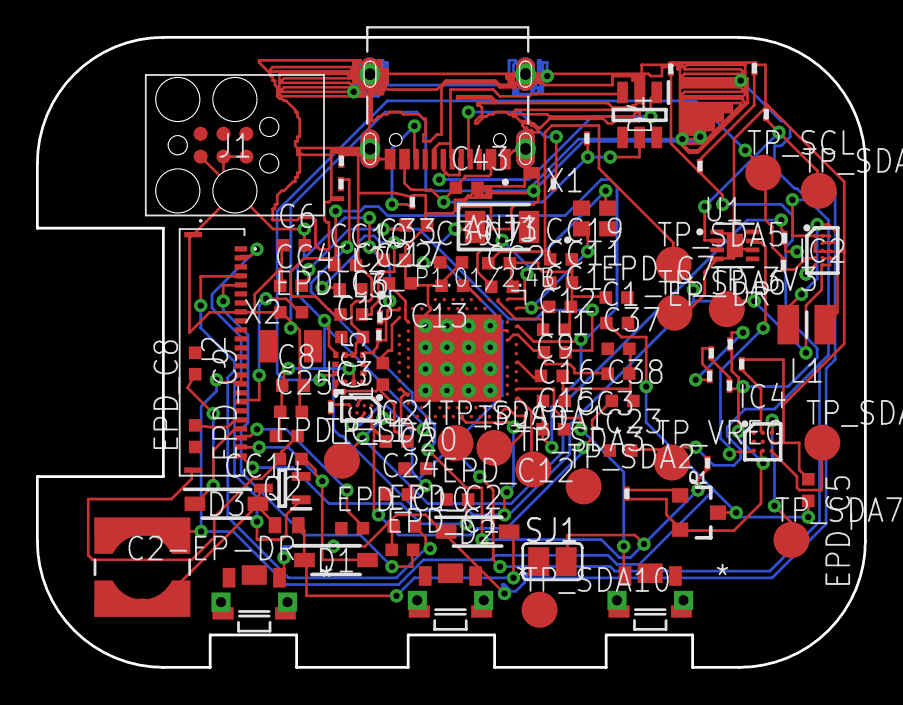
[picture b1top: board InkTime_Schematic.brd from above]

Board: 2 copper layers, 46.0 x 35.0 mm, 105 parts (0 on the bottom side), 79 nets.

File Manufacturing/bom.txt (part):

Partlist exported from Fusion Hub: bogdanpanaitiu   Project: Default Project  Board: InkTime_Schematic at 19/04/2026 16:12

Qty Value                                                   Device                                                                       Package                                                                                                                Parts                                                                                                                      Description                                                                                                               ARROW_PART_NUMBER ARROW_PRICE-STOCK                                                                                AVAILABILITY CHECK_PRICES                                                                       COPYRIGHT                                                DESCRIPTION                                                                                              DIGI-KEY_PART_NUMBER_1                    DIGI-KEY_PART_NUMBER_2 DIGI-KEY_PART_NUMBER_3                              HEIGHT  JLCPCB MANUFACTURER_NAME   MANUFACTURER_PART_NUMBER                                         MF                 MFR_NAME          MOUSER_PART_NUMBER MOUSER_PRICE-STOCK                                                                                           MP                                                                                                       PACKAGE                     POPULARITY PRICE            PROD_ID                      PURCHASE-URL                                                                                                                               SNAPEDA_LINK                                                                      SPICEMODEL SPICEPREFIX                                                                                                                                     TP_SIGNAL_NAME                                                                      VALUE             
1   0                                                       ESP32_C6_LIBRARY_7_JUMPER_SJ                                                 ESP32_C6_LIBRARY_7_JUMPER_SJ                                                                                           SJ1                                                                                                                        SMD solder JUMPER                                                                                                                                                                                                                                                                                                                                                                                                                                                                                                                                                                                                                                                                                                                                                                                                                                                                                                                                                                                                                                 3                                                                                                                                                                                                                                                                                                                                                                                                                                                                                                                                                      
1   0.1uF                                                   GRM011R60J152KE01L_1_GRM011R60J152KE01L                                      GRM011R60J152KE01L_1_0201                                                                                              C4                                                                                                                         Check availability                                                                                                                                                                                                                                                                                                                                                                                                                                                                                                                                                                                                                                                                                                                                                                                                                                                                                                                                                                                                                                                                                                                                                                                                                                                                                                                                                                                                                                                                                                                                                                                       
1   0.1uF                                                   NORDIC_NRF_3_CAPACITOR_0402_M                                                NORDIC_NRF_3_RESC0402_M                                                                                                C23                                                                                                                        Generic chip capacitor                                                                                                                                                                                                                                                                                                                                                                                                                                                                                                                                                                                                                                                                                                                                                                                                                                                                                                                                                                                                                                                                                                                                                                                                                                                                                                                                                                                                                                                                                                                                                                                   
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
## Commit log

2026-04-10 Include Apache License 2.0
    Added the Apache License 2.0 to the project.
2026-04-10 Remove duplicate project title from README
2026-04-10 final

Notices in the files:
parts and their libraries:
COPYRIGHT: Copyright (C) 2024 Ultra Librarian. All rights reserved.
COPYRIGHT: Copyright (C) 2025 Ultra Librarian. All rights reserved.
